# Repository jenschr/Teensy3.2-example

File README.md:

# Teensy3.2-example
A verified example PCB based on the Teensy 3.2 schematics. This repository holds the Kicad files to create your own Teensy 3.2 PCB. Design notes can be found on [my blog](https://flashgamer.com/blog/comments/teensy-3.2-kicad-example).

I'm a consultant based in Oslo/Norway, so [get in touch](https://maketronics.no/about/) if you need custom hardware based on Teensy 4.x (Since Teensy 3.x is no longer feasible due to parts shortage)

Pictures of the finished board can be [found here](images/).

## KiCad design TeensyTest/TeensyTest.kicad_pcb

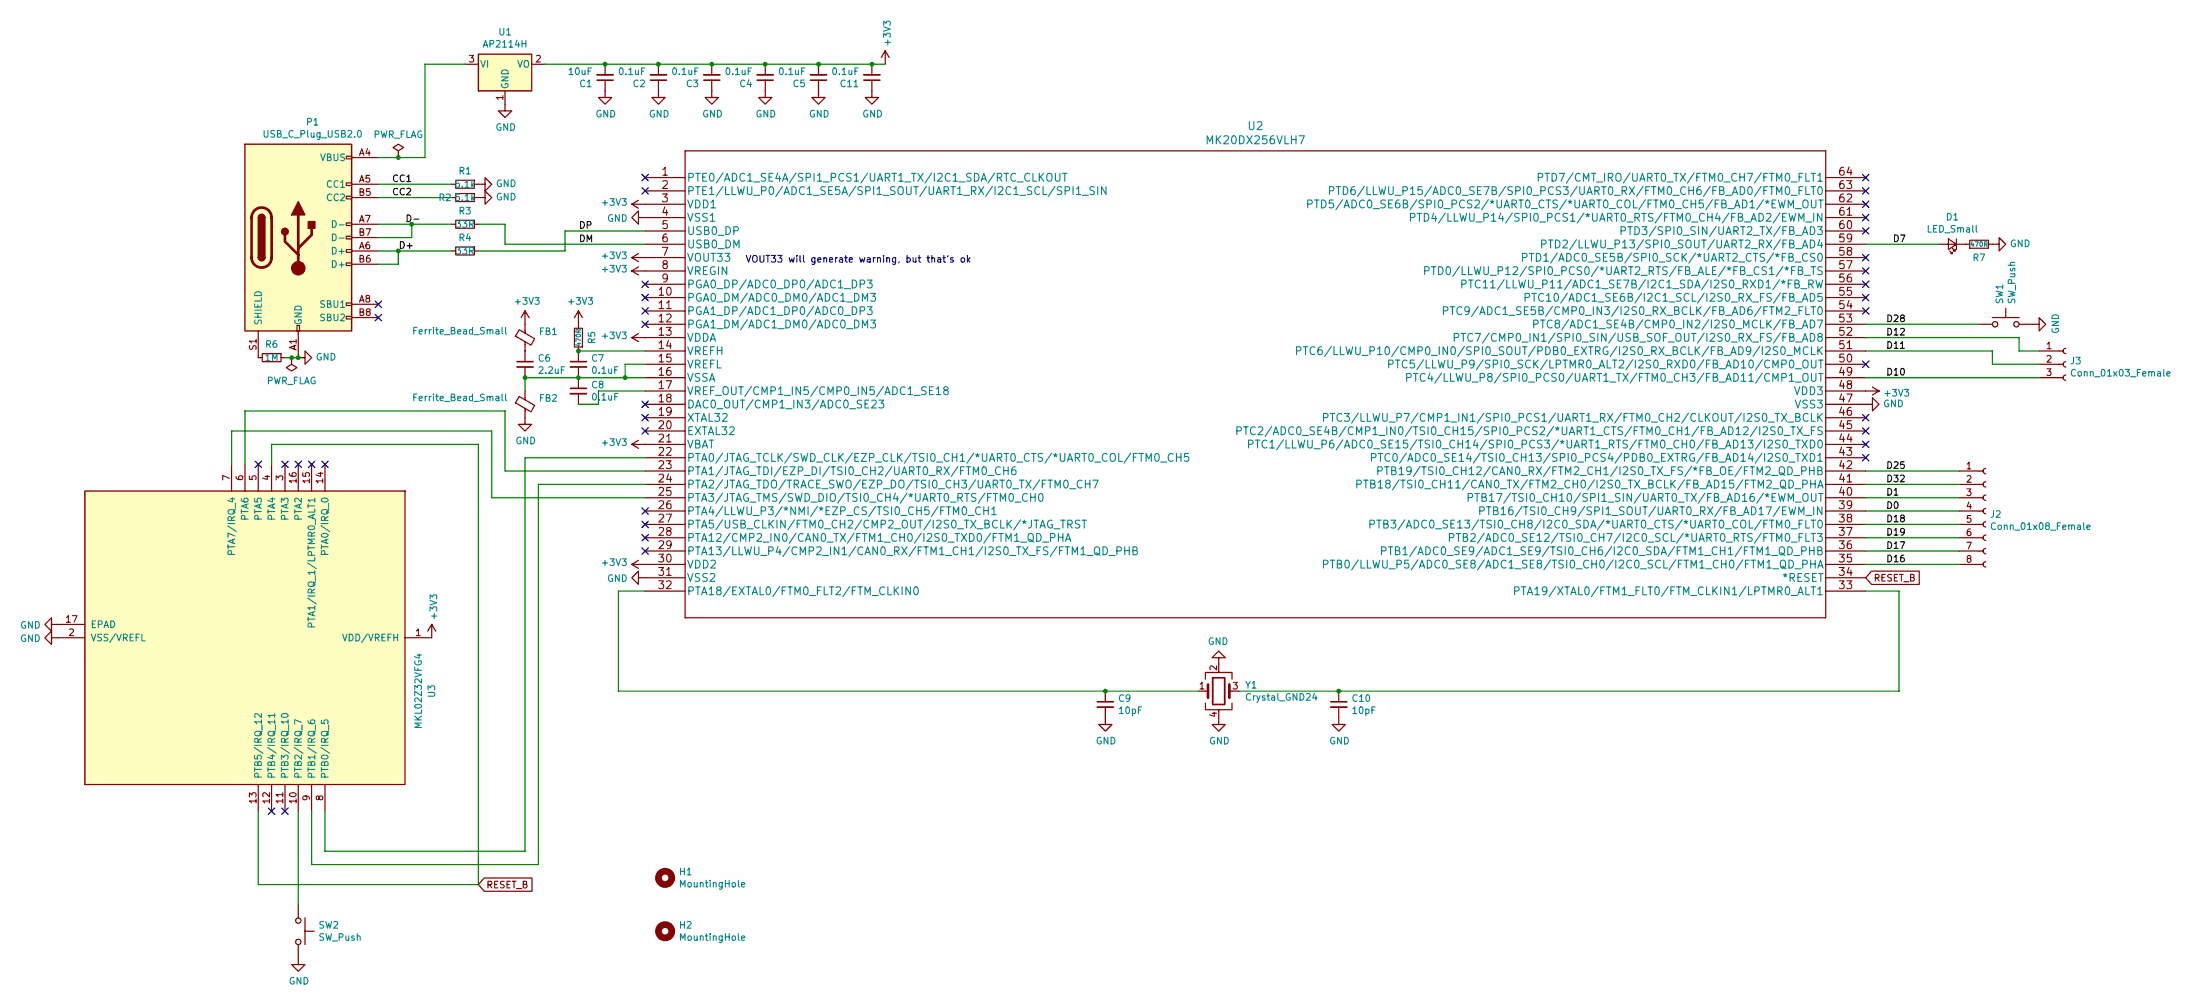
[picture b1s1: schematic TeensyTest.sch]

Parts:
C1: 10uF; C_0805_2012Metric
C2, C3, C4, C5, C7, C8, C11: 0.1uF; C_0603_1608Metric
C6: 2.2uF; R_0603_1608Metric
C9, C10: 10pF; C_0603_1608Metric; MPN 885012006002‎
D1: LED_Small; LED_0603_1608Metric
FB1, FB2: Ferrite_Bead_Small; R_0805_2012Metric; MPN MZ1608-601Y
H1, H2: MountingHole; MountingHole_3.2mm_M3_DIN965_Pad
J2: Conn_01x08_Female; PinHeader_1x08_P2.54mm_Vertical
J3: Conn_01x03_Female; PinHeader_1x03_P2.54mm_Vertical
P1: USB_C_Plug_USB2.0; TYPE-C-31-M-12; MPN TYPE-C-31-M-12
R1, R2: 5.1k; R_0603_1608Metric
R3, R4: 33R; R_0603_1608Metric
R5, R7: 470R; R_0603_1608Metric
R6: 1M; R_0603_1608Metric
SW1, SW2: SW_Push; SW_SPST_EVQQ2; MPN EVQ-Q2B03W
U1: AP2114H; SOT-223-3_TabPin2; MPN AP2114H-3.3TRG1
U2: MK20DX256VLH7; MPN MK20DX256VLH7
U3: MKL02Z32VFG4; QFN-16-1EP_3x3mm_P0.5mm_EP1.8x1.8mm
Y1: Crystal_GND24; Crystal_SMD_Abracon_ABM3B-4Pin_5.0x3.2mm; MPN ABM3B-16.000MHZ-10-1-U-T

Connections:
+3V3: C1.2, C2.2, C3.2, C4.2, C5.2, C11.2, FB1.1, R5.2, U1.2 (VO), U2.3 (VDD1), U2.7 (VOUT33), U2.8 (VREGIN), U2.13 (VDDA), U2.21 (VBAT), U2.30 (VDD2), U2.48 (VDD3), U3.1 (VDD/VREFH)
/CC1: P1.A5 (CC1), R1.2
/CC2: P1.B5 (CC2), R2.2
/D0: J2.4, U2.39 (PTB16/TSI0_CH9/SPI1_SOUT/UART0_RX/FB_AD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)
/D1: J2.3, U2.40 (PTB17/TSI0_CH10/SPI1_SIN/UART0_TX/FB_AD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)
/D7: D1.2 (A), U2.59 (PTD2/LLWU_P13/SPI0_SOUT/UART2_RX/FB_AD4)
/D10: J3.3, U2.49 (PTC4/LLWU_P8/SPI0_PCS0/UART1_TX/FTM0_CH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)
/D11: J3.2, U2.51 (PTC6/LLWU_P10/CMP0_IN0/SPI0_SOUT/PDB0_E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)
/D12: J3.1, U2.52 (PTC7/CMP0_IN1/SPI0_SIN/USB_SOF_OUT/I2S0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)
/D16: J2.8, U2.35 (PTB0/LLWU_P5/ADC0_SE8/ADC1_SE8/TSI0_CH0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)
/D17: J2.7, U2.36 (PTB1/ADC0_SE9/ADC1_SE9/TSI0_CH6/I2C0_SD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)
/D18: J2.5, U2.38 (PTB3/ADC0_SE13/TSI0_CH8/I2C0_SDA/*UART0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)
/D19: J2.6, U2.37 (PTB2/ADC0_SE12/TSI0_CH7/I2C0_SCL/*UART0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)
/D25: J2.1, U2.42 (PTB19/TSI0_CH12/CAN0_RX/FTM2_CH1/I2S0_T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)
/D28: SW1.1, U2.53 (PTC8/ADC1_SE4B/CMP0_IN2/I2S0_MCLK/FB_AD7)
/D32: J2.2, U2.41 (PTB18/TSI0_CH11/CAN0_TX/FTM2_CH0/I2S0_T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)
/D+: P1.A6 (D+), P1.B6 (D+), R4.2
/D-: P1.A7 (D-), P1.B7 (D-), R3.2
/DM: R3.1, U2.6 (USB0_DM)
/DP: R4.1, U2.5 (USB0_DP)
GND: C1.1, C2.1, C3.1, C4.1, C5.1, C9.2, C10.2, C11.1, FB2.2, P1.A1 (GND), P1.A12 (GND), P1.B1 (GND), P1.B12 (GND), R1.1, R2.1, R6.1, R7.2, SW1.2, SW2.2, U1.1 (GND), U2.4 (VSS1), U2.31 (VSS2), U2.47 (VSS3), U3.2 (VSS/VREFL), U3.17 (EPAD), Y1.2, Y1.4
unnamed: C6.1, FB1.2
unnamed: C6.2, C7.2, C8.1, FB2.1, U2.15 (VREFL), U2.16 (VSSA)
unnamed: C7.1, R5.1, U2.14 (VREFH)
unnamed: C8.2, U2.17 (VREF_OUT/CMP1_IN5/CMP0_IN5/ADC1_SE18)
unnamed: C9.1, U2.32 (PTA18/EXTAL0/FTM0_FLT2/FTM_CLKIN0), Y1.1
unnamed: C10.1, U2.33 (PTA19/XTAL0/FTM1_FLT0/FTM_CLKIN1/LPTMR0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), Y1.3
unnamed: D1.1 (K), R7.1
unnamed: P1.S1 (SHIELD), R6.2
unnamed: SW2.1, U3.10 (PTB2/IRQ_7)
unnamed: U2.22 (PTA0/JTAG_TCLK/SWD_CLK/EZP_CLK/TSI0_CH1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), U3.8 (PTB0/IRQ_5)
unnamed: U2.23 (PTA1/JTAG_TDI/EZP_DI/TSI0_CH2/UART0_RX/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), U3.6 (PTA6)
unnamed: U2.24 (PTA2/JTAG_TDO/TRACE_SWO/EZP_DO/TSI0_CH3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), U3.9 (PTB1/IRQ_6)
unnamed: U2.25 (PTA3/JTAG_TMS/SWD_DIO/TSI0_CH4/*UART0_R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), U3.7 (PTA7/IRQ_4)
RESET_B: U2.34 (*RESET), U3.4 (PTA4), U3.13 (PTB5/IRQ_12)
VBUS: P1.A4 (VBUS), P1.A9 (VBUS), P1.B4 (VBUS), P1.B9 (VBUS), U1.3 (VI)

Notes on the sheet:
VOUT33 will generate warning, but that’s ok

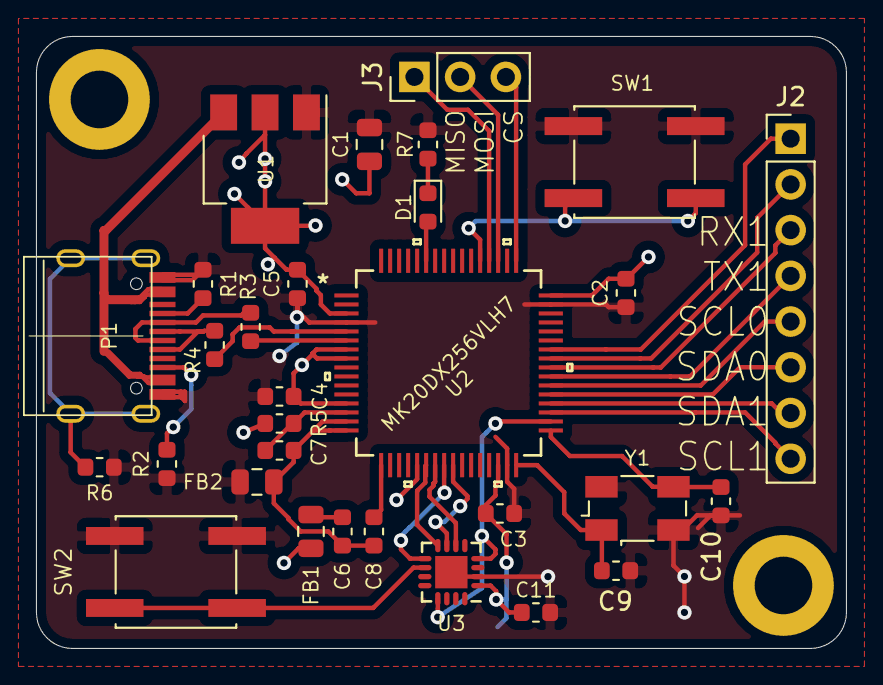
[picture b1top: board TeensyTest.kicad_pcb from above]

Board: 2 copper layers, 45.0 x 34.0 mm, 32 parts (0 on the bottom side), 36 nets.

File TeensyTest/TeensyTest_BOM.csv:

"Ref","Value","Footprint","MPN","MFGR"
"C1","10uF","Capacitor_SMD:C_0805_2012Metric","",""
"C2","0.1uF","Capacitor_SMD:C_0603_1608Metric","",""
"C3","0.1uF","Capacitor_SMD:C_0603_1608Metric","",""
"C4","0.1uF","Capacitor_SMD:C_0603_1608Metric","",""
"C5","0.1uF","Capacitor_SMD:C_0603_1608Metric","",""
"C6","2.2uF","Resistor_SMD:R_0603_1608Metric","",""
"C7","0.1uF","Capacitor_SMD:C_0603_1608Metric","",""
"C8","0.1uF","Capacitor_SMD:C_0603_1608Metric","",""
"C9","10pF","Capacitor_SMD:C_0603_1608Metric","885012006002‎","Wurth"
"C10","10pF","Capacitor_SMD:C_0603_1608Metric","885012006002‎","Wurth"
"D1","LED_Small","LED_SMD:LED_0603_1608Metric","",""
"FB1","Ferrite_Bead_Small","Resistor_SMD:R_0805_2012Metric","MZ1608-601Y","Bourns"
"FB2","Ferrite_Bead_Small","Resistor_SMD:R_0805_2012Metric","MZ1608-601Y","Bourns"
"H1","MountingHole","MountingHole:MountingHole_3.2mm_M3_DIN965_Pad","",""
"H2","MountingHole","MountingHole:MountingHole_3.2mm_M3_DIN965_Pad","",""
"J2","Conn_01x08_Female","Connector_PinHeader_2.54mm:PinHeader_1x08_P2.54mm_Vertical","",""
"J3","Conn_01x03_Female","Connector_PinHeader_2.54mm:PinHeader_1x03_P2.54mm_Vertical","",""
"P1","USB_C_Plug_USB2.0","USB-C-Power-tester:TYPE-C-31-M-12","TYPE-C-31-M-12","Korean Hroparts Elec"
"R1","5.1k","Resistor_SMD:R_0603_1608Metric","",""
"R2","5.1k","Resistor_SMD:R_0603_1608Metric","",""
"R3","33R","Resistor_SMD:R_0603_1608Metric","",""
"R4","33R","Resistor_SMD:R_0603_1608Metric","",""
"R5","470R","Resistor_SMD:R_0603_1608Metric","",""
"R6","1M","Resistor_SMD:R_0603_1608Metric","",""
"R7","470R","Resistor_SMD:R_0603_1608Metric","",""
"SW1","SW_Push","Button_Switch_SMD:SW_SPST_EVQQ2","EVQ-Q2B03W","Panasonic"
"SW2","SW_Push","Button_Switch_SMD:SW_SPST_EVQQ2","EVQ-Q2B03W","Panasonic"
"U1","AP2114H","Package_TO_SOT_SMD:SOT-223-3_TabPin2","AP2114H-3.3TRG1",""
"U2","MK20DX256VLH7","footprints:MK20DX256VLH7","MK20DX256VLH7","NXP"
"U3","MKL02Z32VFG4","Package_DFN_QFN:QFN-16-1EP_3x3mm_P0.5mm_EP1.8x1.8mm","","PJRC"
"Y1","Crystal_GND24","Crystal:Crystal_SMD_Abracon_ABM3B-4Pin_5.0x3.2mm","ABM3B-16.000MHZ-10-1-U-T","Abracon"
" "," "
"Source:","/Users/jensa/Dropbox/Hardware/Teensy3.2-example/TeensyTest/TeensyTest.sch"
"Date:","2020 July 05, Sunday 18:20:21"
"Tool:","Eeschema (5.1.2-1)-1"
"Component Count:","31"

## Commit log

2020-07-05 First commit after verifying v2 of the board
2020-07-05 Added BOM, added more pictures, added MPN's for some parts
2020-07-05 Added picture of the first board that had data lines swapped. Fixed with bodge wires...
2020-07-17 Moved C4 closer to pins 7 & 8
2020-07-17 Added extra 100nF cap for MKL02
2020-09-10 added Teensy3.2 schematic as reference, added CLK pin for SPI comms
2021-03-17 Added naming to all files, pdf schematic
2021-03-17 Updated PDF

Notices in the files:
parts and their libraries:
Copyright 2016 Accelerated Designs. All rights reserved.
